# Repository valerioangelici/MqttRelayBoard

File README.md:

# esp8266MqttRelayBoard
Project for a relay board powered by a esp-12e communicating with a MQTT server

Experimental projects for a esp8266 (esp-12e) driven relay board communicating with the MQTT protocol.
I'm planning to use these with openhab to drive loads with a not high power consumption.
Everything in this project is still experimental so make your valutations before using this material.

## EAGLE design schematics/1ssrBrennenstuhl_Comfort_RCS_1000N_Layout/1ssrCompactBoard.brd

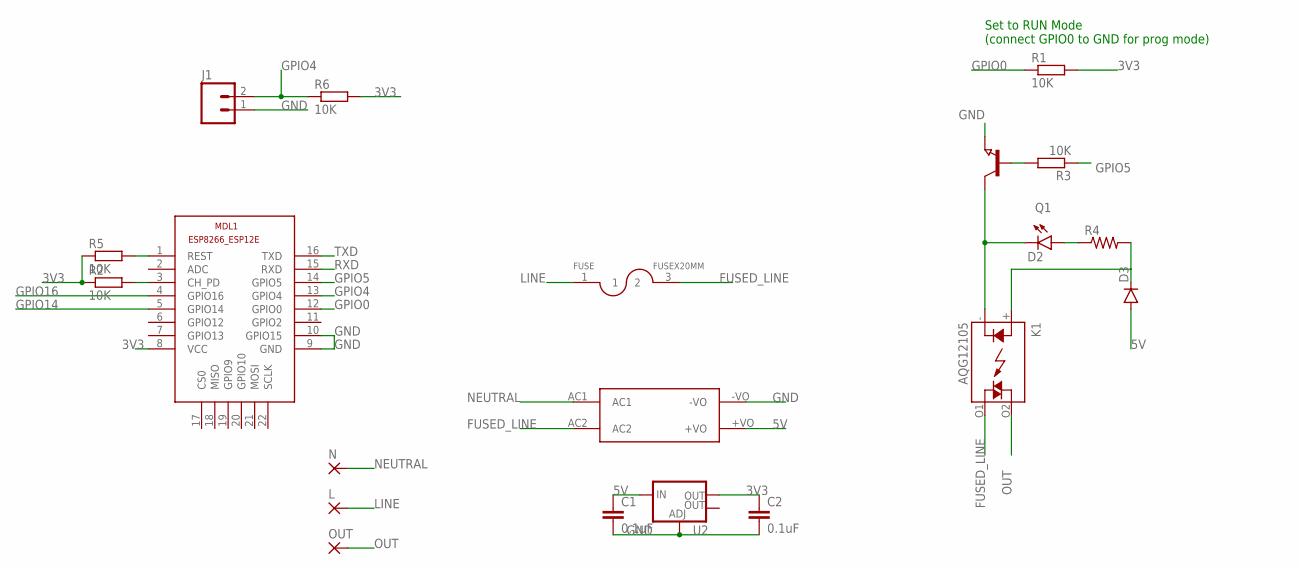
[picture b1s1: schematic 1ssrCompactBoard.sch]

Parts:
C1, C2: 0.1uF; 0603-CAP
D2: LED0603; LED-0603
D3: DIODESMA; SMA-DIODE
FUSE: FUSEX20MM; FUSE_5MM
J1: M02PTH3; 1X02_LONGPADS
K1: AQG12105; AQG
L: 3,81/1,1
MDL1: ESP8266-12EESP8266-ESP12E; ESP8266-ESP12E
N: 3,81/1,1
OUT: 3,81/1,1
Q1: NPN-TRANSISTOR_SOT23; SOT23
R1, R2, R3, R5, R6: 10K; R0805
R4: RESISTOR0603; 0603-RES
U2: V_REG_LM1117SOT223; SOT223
U$4: HLK-PM01

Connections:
3V3: C2.1, MDL1.8 (VCC), R1.2, R2.1, R5.1, R6.2, U2.2 (OUT)
5V: C1.1, D3.A, U2.3 (IN), U$4.+VO
FUSED_LINE: FUSE.3 (2), K1.O1 (DS2), U$4.AC2
GND: C1.2, C2.2, J1.1, MDL1.9 (GND), MDL1.10 (GPIO15), Q1.2 (E), U2.1 (ADJ), U$4.-VO
GPIO0: MDL1.12 (GPIO0), R1.1
GPIO4: J1.2, MDL1.13 (GPIO4), R6.1
GPIO5: MDL1.14 (GPIO5), R3.1
GPIO14: MDL1.5 (GPIO14)
GPIO16: MDL1.4 (GPIO16)
LINE: FUSE.1, L.1
unnamed: D2.A, R4.1
unnamed: D3.C, K1.+ (A), R4.2
unnamed: MDL1.1 (REST), R5.2
unnamed: MDL1.3 (CH_PD), R2.2
unnamed: D2.C, K1.- (K), Q1.3 (C)
unnamed: Q1.1 (B), R3.2
NEUTRAL: N.1, U$4.AC1
OUT: K1.O2 (DS1), OUT.1
RXD: MDL1.15 (RXD)
TXD: MDL1.16 (TXD)

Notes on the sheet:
Set to RUN Mode (connect GPIO0 to GND for prog mode)

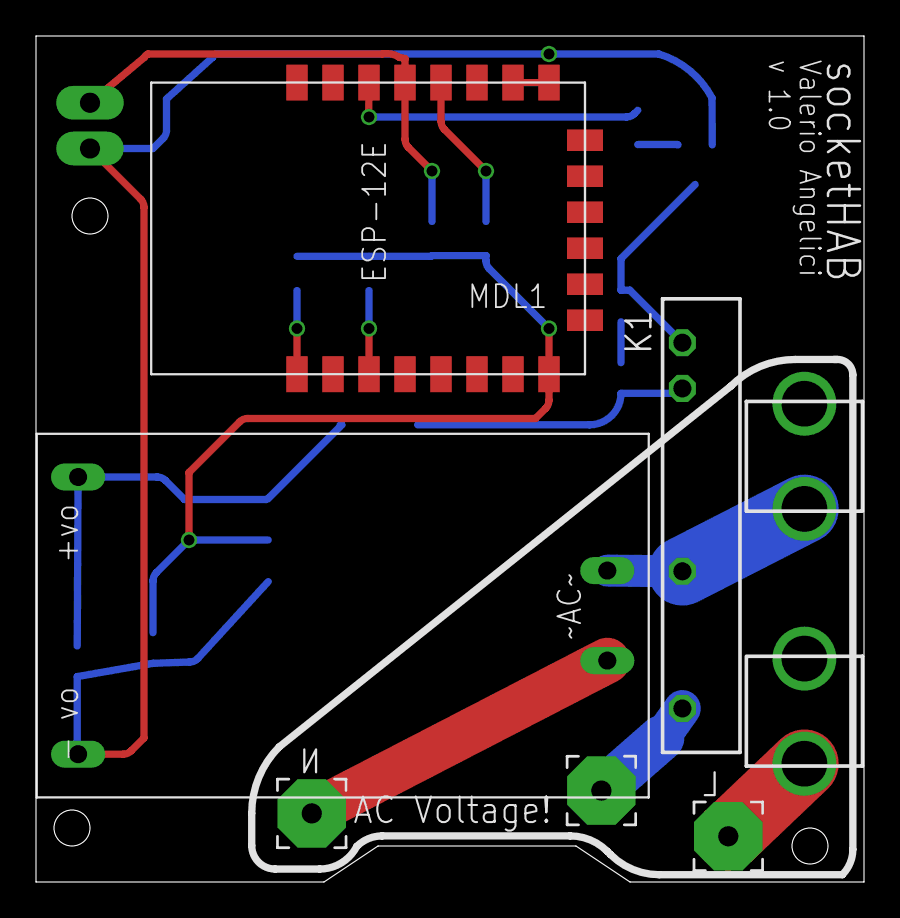
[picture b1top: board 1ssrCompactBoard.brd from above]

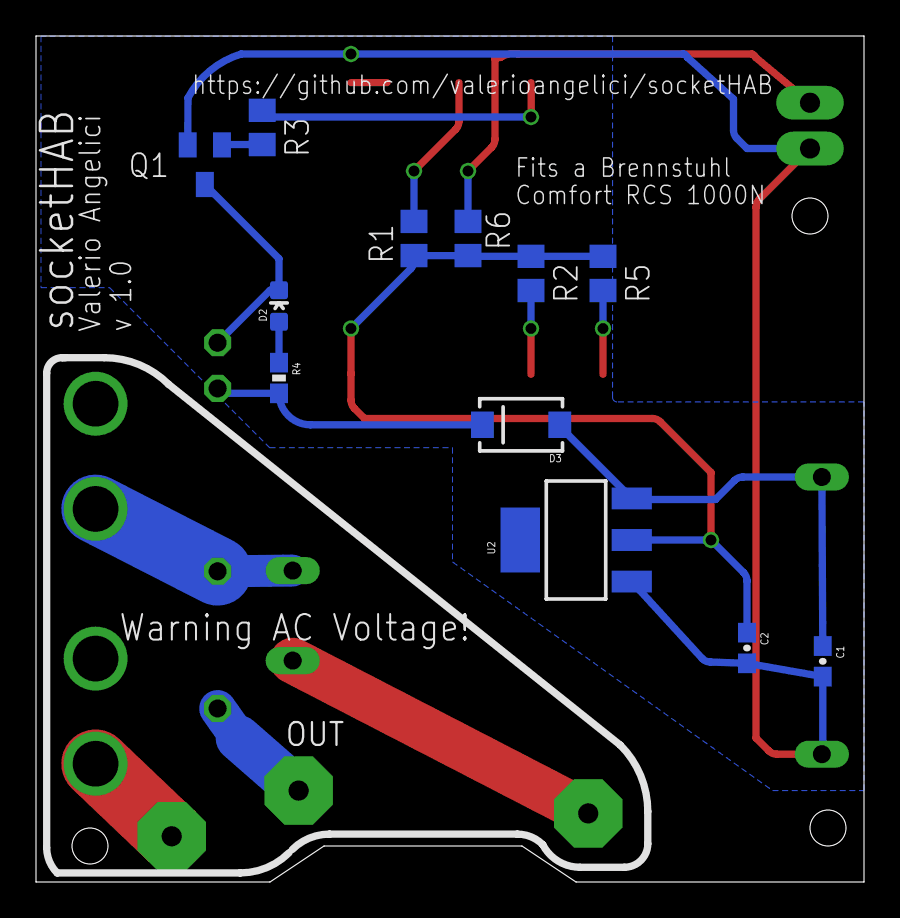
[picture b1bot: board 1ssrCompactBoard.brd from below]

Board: 2 copper layers, 46.0 x 47.0 mm, 20 parts (12 on the bottom side), 16 nets.

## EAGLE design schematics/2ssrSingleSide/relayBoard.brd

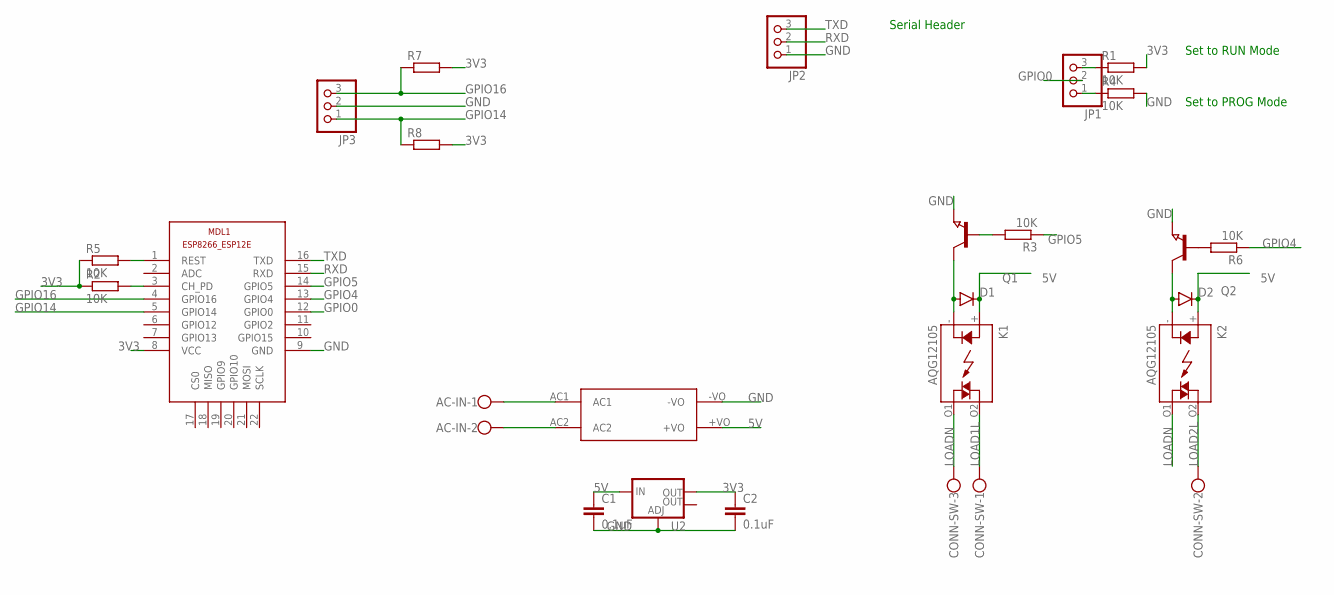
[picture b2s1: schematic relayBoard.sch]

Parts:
AC-IN: W237-102
C1, C2: 0.1uF; 0603-CAP
CONN-SW: W237-103
D1, D2: DIODESMA; SMA-DIODE
JP1, JP2, JP3: PINHD-1X3; 1X03
K1, K2: AQG12105; AQG
MDL1: ESP8266-12EESP8266-ESP12E; ESP8266-ESP12E
Q1, Q2: NPN-TRANSISTOR_SOT23; SOT23
R1, R2, R3, R4, R5, R6: 10K; R0805
R7, R8: R-EU_R0805; R0805
U2: V_REG_LM1117SOT223; SOT223
U$4: HLK-PM01

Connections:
3V3: C2.1, MDL1.8 (VCC), R1.2, R2.1, R5.1, R7.2, R8.2, U2.2 (OUT)
5V: C1.1, D1.C, D2.C, K1.+ (A), K2.+ (A), U2.3 (IN), U$4.+VO
GND: C1.2, C2.2, JP2.1, JP3.2, MDL1.9 (GND), Q1.2 (E), Q2.2 (E), R4.2, U2.1 (ADJ), U$4.-VO
GPIO0: JP1.2, MDL1.12 (GPIO0)
GPIO4: MDL1.13 (GPIO4), R6.1
GPIO5: MDL1.14 (GPIO5), R3.1
GPIO14: JP3.1, MDL1.5 (GPIO14), R8.1
GPIO16: JP3.3, MDL1.4 (GPIO16), R7.1
LOAD1L: CONN-SW.1, K1.O2 (DS1)
LOAD2L: CONN-SW.2, K2.O2 (DS1)
LOADN: CONN-SW.3, K1.O1 (DS2), K2.O1 (DS2)
unnamed: JP1.3, R1.1
unnamed: AC-IN.1, U$4.AC1
unnamed: JP1.1, R4.1
unnamed: AC-IN.2, U$4.AC2
unnamed: MDL1.1 (REST), R5.2
unnamed: D2.A, K2.- (K), Q2.3 (C)
unnamed: Q2.1 (B), R6.2
unnamed: MDL1.3 (CH_PD), R2.2
unnamed: D1.A, K1.- (K), Q1.3 (C)
unnamed: Q1.1 (B), R3.2
RXD: JP2.2, MDL1.15 (RXD)
TXD: JP2.3, MDL1.16 (TXD)

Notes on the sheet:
Set to RUN Mode
Set to PROG Mode
Serial Header

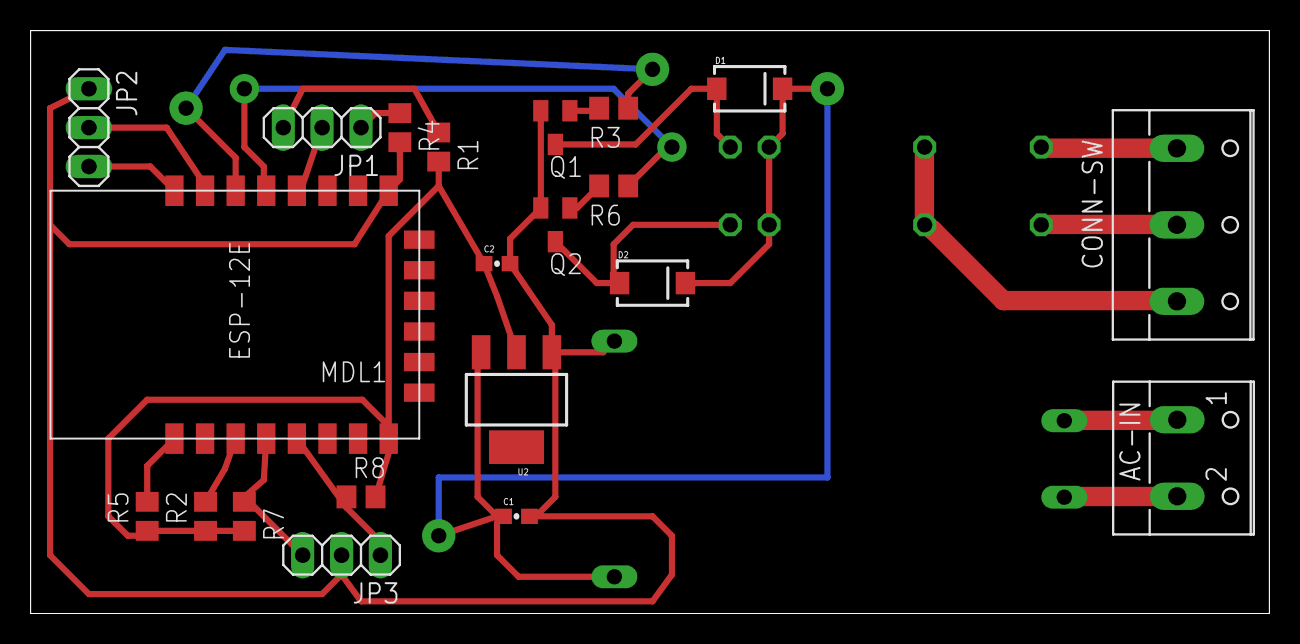
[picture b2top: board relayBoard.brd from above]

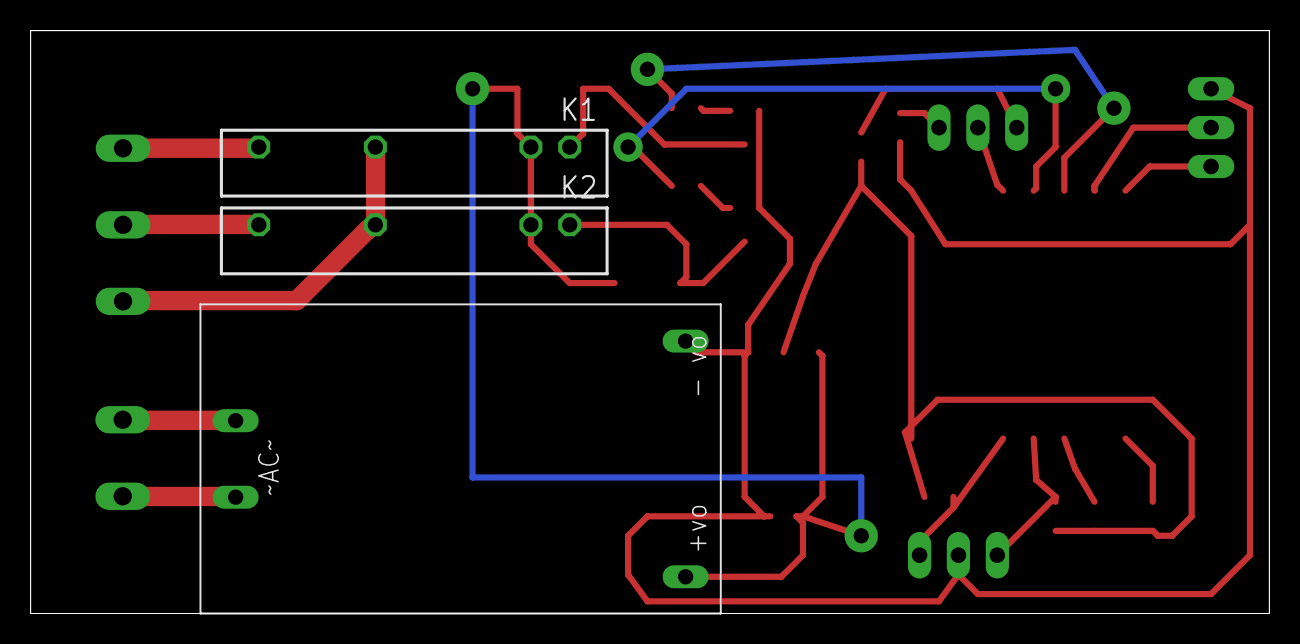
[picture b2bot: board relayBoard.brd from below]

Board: 2 copper layers, 81.0 x 38.1 mm, 24 parts (3 on the bottom side), 23 nets.

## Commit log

2016-02-12 board and schematics work in progress
2016-02-15 code and schematic modifications
2016-02-17 moved schematics and board
2016-02-17 Create README.md file
2016-02-29 Added Brennenstuhl_Comfort_RCS_1000N_Layout work in progress
2016-02-29 added mysecrets.h to git ignore to avoid committing my secrets config
2016-03-02 placed fuse on pcb
2016-03-04 board routing work in progress
2016-03-08 added eagle section to .gitIgnore and removed epf files
2016-03-09 silkscreen wip
2016-03-18 board work in progress
2016-09-08 added missing connection on pin gpio15
2016-09-08 added ground plane
2016-09-08 added setPhyMode and mode to improve wifi stability
2016-09-16 added pdf exports
2016-09-20 diode moved
2016-09-20 copied arduino code
2016-09-22 long press switch code
2016-09-22 long press added
2018-04-27 working on a new Arduino code version
2018-04-30 code fixes
2018-04-30 config fixes

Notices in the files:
parts and their libraries:
SparkFun-Capacitors: Licensing: Creative Commons ShareAlike 4.0 International - https://creativecommons.org/licenses/by-sa/4.0
